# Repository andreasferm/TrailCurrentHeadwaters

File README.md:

# TrailCurrent In-Vehicle Compute

> [!CAUTION]
> **Personal fork adapting to a new module [Australis](https://github.com/andreasferm/TrailCurrentAustralis) with the aim to monitor 1-8 enclosed rooms in a dogtrailer** This is definitely a work in progress
> **The Radxa Dragon Q6A variant is a work in progress and is not recommended for use yet.** Further hardware and field testing is required before it should be considered shippable. Use the **CM5 build** for any real deployment.

Dockerized edge gateway with MQTT broker, tile server, and local dashboards. Part of the [TrailCurrent](https://trailcurrent.com) open-source vehicle platform.

## Quick Navigation

| I want to... | Go here |
|--------------|---------|
| Set up a development environment | [Development Setup](#development-setup) below |
| Build a CM5 image or deployment package | [Building for CM5 Devices](#building-for-cm5-devices) below |
| Flash and set up a new CM5 device | [CM5/SETUP.md](CM5/SETUP.md) |
| Update an existing device | [PI_DEPLOYMENT.md](PI_DEPLOYMENT.md) |
| Understand cloud OTA updates | [OTA_DEPLOYMENT_IMPLEMENTATION.md](OTA_DEPLOYMENT_IMPLEMENTATION.md#cloud-to-pi-ota-deployment-deployment-watcher) |

## Prerequisites

- **Hardware:** Raspberry Pi Compute Module 5 (CM5) on a standard carrier board with Waveshare RS485 CAN HAT (B) — no custom components or soldering required. The CM5 + carrier board replaces the previous Pi 5 + NVME Base + custom CAN HAT stack: it's more compact, more readily available, cheaper, and can be fully assembled from off-the-shelf parts.
- **Docker Engine** (or Docker Desktop) with the `compose` plugin and `buildx`
- **Git**

---

## Development Setup

This gets your local development environment running with hot-reload and debugging enabled. All services build from local Dockerfiles for the host platform.

### Step 1: Clone and configure environment

```bash
git clone <REPO_URL>
cd TrailCurrentHeadwaters
git config core.hooksPath .githooks
docker buildx use default
cp .env.example .env
```

### Step 2: Generate secure random values

```bash
# Generate ENCRYPTION_KEY (64 character hex string)
openssl rand -hex 32
```

Copy the value into `ENCRYPTION_KEY` in `.env`.

### Step 3: Edit `.env` and set your values

- `ENCRYPTION_KEY` - Paste the value from step 2
- `ADMIN_PASSWORD` - Strong password for system admin access
- `MQTT_USERNAME` - Username for MQTT broker
- `MQTT_PASSWORD` - Password for MQTT broker (plain text - auto-added to broker at startup)
- `TLS_CERT_HOSTNAME` - Your device's hostname (e.g., `trailcurrent01.local`)

### Step 4: Generate SSL certificates

```bash
./scripts/generate-certs.sh
# Select option 1 for Development or option 2 for Production
```

See [SSL Certificate Generation](#ssl-certificate-generation) for details.

### Step 5: Obtain map tiles

The tileserver requires a pre-generated mbtiles file to serve map data.

```bash
mkdir -p data/tileserver
# Place your tiles file at: data/tileserver/map.mbtiles
```

**How to get tiles:**
- **Download from OpenStreetMap:** Use the [PbfTileConverter](https://github.com/onthegomap/planetiler) utility or a service like [Protomaps](https://protomaps.com/) to generate tiles from OSM data (see [DOCS/UpdatingMapTiles.md](DOCS/UpdatingMapTiles.md))
- **Copy from a team member:** Copy `map.mbtiles` from an existing machine

A single US state (~200 MB - 2 GB) works fine for development. Full US coverage is ~10-25 GB.

### Step 6: Build and start in development mode

```bash
docker compose -f docker-compose.yml -f docker-compose.dev.yml up -d --build
```

The `--build` flag ensures all images are built from local Dockerfiles for your host platform. Development mode enables:
- Hot-reload for frontend and backend code changes
- Node.js debug port (9229) for VSCode debugger attachment
- MongoDB accessible on localhost:27017
- Tileserver styles hot-reload

Containers will automatically:
- Create the mosquitto password file from your credentials
- Initialize all services with consistent credentials
- Mount the SSL certificates for HTTPS/MQTTS communication
- Load map tiles from the mbtiles file

### Verification Checklist

After startup, verify all services are healthy:

```bash
# All 5 containers should be running
docker compose ps

# Frontend loads
curl -k https://localhost/

# Tileserver healthy
curl http://localhost:8080/health

# Map style served
curl -s http://localhost:8080/styles/3d-dark/style.json | head -5

# Font glyphs available
curl -s -o /dev/null -w "%{http_code}" "http://localhost:8080/fonts/Noto%20Sans%20Regular/0-255.pbf"
# Expected: 200
```

**Access the web UI:** https://localhost (accept the self-signed certificate warning)

### Security Notes

- `.env` is in `.gitignore` - will never be committed
- Use strong, randomly generated passwords for all credentials
- All values in `.env.example` are placeholders only
- Passwords are auto-hashed/auto-configured at container startup

---

## Building for CM5 Devices

There are two ways to get the application onto a CM5 device:

### Option A: Build a Complete CM5 Image (Recommended for New Devices)

The CM5 image includes everything — OS, Docker, application containers, map
tiles, and configuration. After flashing, the user just sets passwords via
an interactive wizard on first SSH login.

**Prerequisites (files not in the repo that you must provide):**

| File | How to get it |
|------|---------------|
| `images/*.tar` | Run `./build-and-save-images.sh` (builds ARM64 Docker images) |
| `data/tileserver/map.mbtiles` | Download from OSM data or copy from a team member (see [DOCS/UpdatingMapTiles.md](DOCS/UpdatingMapTiles.md)) |

**Build the image:**
```bash
# 1. Build ARM64 Docker images (~10 min first time)
./build-and-save-images.sh

# 2. Ensure map.mbtiles exists at data/tileserver/map.mbtiles

# 3. Build the CM5 image (bakes in Docker images, map tiles, app code, configs)
cd CM5/image
sudo ./build.sh myuser mypassword
```

The output image (~28 GB) is flashed to NVMe via `dd`. See [CM5/SETUP.md](CM5/SETUP.md)
for the full flashing and setup procedure.

### Option B: Build a Deployment Package (For Updating Existing Devices)

For updating devices that already have an image flashed, create an offline
deployment zip:

```bash
# Build everything and create the zip
./create-deployment-package.sh --version=1.0.0
```

This will:
1. Build all 4 service images for `linux/arm64` (plus pull `mongo:7`)
2. Save images as `.tar` files in `images/`
3. Fetch MCU firmware from GitHub releases (if available)
4. Package everything into `trailcurrent-deployment-1.0.0.zip`

**Transfer and deploy to device:**
```bash
scp trailcurrent-deployment-1.0.0.zip myuser@headwaters.local:~
# On the device:
unzip -o trailcurrent-deployment-1.0.0.zip && ./deploy.sh
```

Replace `myuser` with the username configured when the CM5 image was built.

See [PI_DEPLOYMENT.md](PI_DEPLOYMENT.md) for detailed deployment instructions.

> **Note:** `build-and-save-images.sh` is a prerequisite for both options.
> The CM5 image build (`build.sh`) and the deployment package
> (`create-deployment-package.sh`) both consume the `images/*.tar` files
> it produces.

---

## Architecture

### Services

The application runs 5 Docker containers:

| Service | Purpose |
|---------|---------|
| **frontend** | nginx serving the MapLibre GL PWA (HTTPS on port 443) |
| **backend** | Node.js Express API with MQTT, CAN bridge, and cloud bridge |
| **mosquitto** | Eclipse Mosquitto MQTT broker (TLS on port 8883) |
| **mongodb** | MongoDB 7 document database |
| **tileserver** | Custom vector tile server with styles, fonts, and sprites |

### CAN Bus Bridge

The backend includes a built-in CAN bridge service (`src/services/can-bridge.js`) that:
- Subscribes to `can/inbound` MQTT messages from the host-side Python CAN-to-MQTT bridge
- Routes by CAN identifier and parses bit-array data into structured JSON
- Publishes to `local/*` MQTT topics (lights, relays, energy, GPS, air quality, leveling)
- Sends outbound CAN commands for light toggles, brightness, and relay control

### Cloud Bridge

When cloud synchronization is enabled in Settings, the backend connects a second MQTT client to the Farwatch cloud broker over cellular LTE (`src/services/cloud-bridge.js`):

- **Cloud to Local (Commands):** `rv/lights/N/command` triggers CAN toggle, `rv/thermostat/command` passes through to local
- **Cloud to Local (Proximity):** `rv/proximity/event` and `rv/proximity/status` are forwarded to `local/proximity/*` and broadcast via WebSocket. These events are published by the Farwatch proximity engine when a registered phone enters or leaves a distance zone around the vehicle. The automation rules themselves execute on Farwatch (publishing light/relay commands via the existing `rv/lights/*/command` and `rv/relays/*/command` topics), so no rule processing happens on the vehicle. The forwarded events are available for future Overlook UI display.
- **Local to Cloud (Status):** Forwarded using three data-saving mechanisms to stay within a 10 GB/month cellular budget:
  - **Change detection** — Messages identical to the last-sent value are suppressed. Lights and relays (65% of raw CAN traffic) broadcast unchanged state every second; change detection eliminates ~99% of these.
  - **Tiered intervals** — Each data type has a minimum send interval: immediate (lights, relays, thermostat — on change only), 5 seconds (energy, GPS position — with threshold bypass for significant changes), 15 seconds (altitude, air quality, leveling), 30 seconds (system stats). GPS time is not forwarded (Farwatch has its own clock).
  - **Heartbeat** — Every 20 seconds, all last-known state is republished to the cloud as a safety net for connection-level failures. In normal operation, state changes are forwarded immediately via MQTT QoS 1.
- **Config sync:** System config snapshot published as retained message on cloud connect, plus forced full-state heartbeat on reconnect

### SMS Notifications

The system can send SMS text messages through a cellular router's `sendsms` command via SSH. This is configured in **Settings > SMS Notifications**:

- **Phone Number** — Destination phone number (e.g., `+15551234567`)
- **Router IP Address** — LAN IP of the cellular router
- **SSH Private Key** — Private key for passwordless SSH as `root` to the router

To set up SSH access to the router:

```bash
# Generate an SSH key (if you don't already have one)
ssh-keygen -t ed25519

# Copy the public key to the router
ssh-copy-id root@<router-ip>
```

The private key (typically `~/.ssh/id_ed25519`) is pasted into the settings field and stored encrypted in the database. Use the **Send Test SMS** button to verify the configuration.

### Alarm System

The alarm feature provides SMS notifications when device state changes are detected. A toggle on the home screen enables/disables the alarm. When enabled, the system monitors CAN bus status messages and sends an SMS when a device's state changes.

**How it works:**

1. The MQTT service tracks the last known state of each device from CAN bus messages
2. When a new status message reports a different state than the cached value, the alarm fires
3. Notifications are grouped by device type, each with its own independent cooldown (default 60 seconds)
4. Multiple state changes within the same group's cooldown window result in a single SMS

**Alarm groups:**

| Group | Source | Trigger |
|-------|--------|---------|
| `light` | PDM/Torrent light controllers | Light state change (on/off) |
| `relay` | Switchback relay modules | Relay state change (on/off) |
| `energy` | Energy monitor | (future) |
| `airquality` | Air quality sensor | (future) |
| `thermostat` | Thermostat | (future) |
| `level` | Leveling system | (future) |
| `gps` | GPS/GNSS | (future) |

Groups are defined in `MqttService.ALARM_GROUPS` in `containers/backend/src/mqtt.js`. Each group can be configured with its own cooldown period, and the architecture supports per-group settings for whether every event or only the first event in a window should trigger an SMS.

**SMS message content:**

- If cloud is enabled: `Unexpected event occurred, check Farwatch for details <cloud_url>`
- If cloud is not enabled: `Unexpected event occurred`

**Requirements:** SMS must be configured and enabled in Settings for alarm notifications to be sent.

### Host-Side Services

Python scripts running as systemd services on the host (outside Docker):
- `can-to-mqtt.py` — Bridges the physical CAN bus (`can0`) to MQTT topics (`can/inbound`, `can/outbound`)
- `discovery-mdns.py` — Discovers MCU modules on the local network via mDNS
- `deployment-watcher.py` — Monitors for OTA deployment updates from the cloud

---

## Project Structure

```
containers/          Dockerfiles for each service
  frontend/          nginx + MapLibre GL web UI
  backend/           Node.js Express API + CAN bridge + cloud bridge
  mosquitto/         Eclipse Mosquitto MQTT broker
  tileserver/        Custom tile server (styles, fonts, sprites)
config/              Version-controlled service configurations
  mosquitto/         mosquitto.conf
data/                Runtime data (gitignored)
  keys/              TLS certificates
  tileserver/        map.mbtiles (~25 GB, not in repo)
images/              ARM64 Docker image tarballs (gitignored, built by build-and-save-images.sh)
local_code/          Python host services (CAN-to-MQTT bridge, deployment watcher, OTA helpers)
scripts/             Utility scripts (cert generation)
CM5/                 CM5 image build system, flashing tools, setup guide
```

**Docker Compose files:**
- `docker-compose.yml` — Production orchestration (5 services)
- `docker-compose.dev.yml` — Development overrides (hot-reload, debug ports)

---

## SSL Certificate Generation

The application uses TLS/SSL for secure communication. Certificates must be generated before running `docker compose up`. The `scripts/generate-certs.sh` script supports two modes:

### Quick Reference

```bash
# Interactive mode (prompts for selection)
./scripts/generate-certs.sh

# Non-interactive mode (development)
./scripts/generate-certs.sh 1

# Non-interactive mode (production)
./scripts/generate-certs.sh 2

# Using environment variable
CERT_MODE=2 ./scripts/generate-certs.sh

# Show help
./scripts/generate-certs.sh --help
```

### Development Certificates (Local Testing)

For local development with `localhost` or `127.0.0.1`:

```bash
./scripts/generate-certs.sh 1
```

**Development certificates include:**
- DNS names: `localhost`, plus your `TLS_CERT_HOSTNAME` from `.env`
- IP addresses: `127.0.0.1`, `::1` (IPv6 localhost)

**Access locally:**
```
https://localhost           - Frontend (HTTPS)
```

Accept the self-signed certificate warning in your browser (one-time).

### Production Certificates (Deployment)

For deployed devices accessed from other machines on the network:

1. **Set your device's hostname** in `.env`:
   ```
   TLS_CERT_HOSTNAME=trailcurrent01.local
   ```

2. **Generate production certificates:**
   ```bash
   ./scripts/generate-certs.sh 2
   ```

3. **Install the CA certificate** (`data/keys/ca.crt`) on devices that will access the web UI.

4. **Access from the network:**
   ```
   https://trailcurrent01.local       - Web UI
   mqtts://trailcurrent01.local:8883  - MQTT broker
   ```

### Regenerating Certificates

Run the script anytime to regenerate. It will prompt before overwriting existing certificates and create backups.

```bash
./scripts/generate-certs.sh
docker compose restart
```

Certificates are automatically protected by `.gitignore`. Never commit them to version control.

---

## Docker

### Running Containers

```bash
# Development mode (hot-reload, debug ports) — always use --build to ensure local images
docker compose -f docker-compose.yml -f docker-compose.dev.yml up -d --build

# Production mode (after verification)
docker compose up -d --build
```

### Docker Networking

**MongoDB Access:**
- Services communicate via Docker's internal network: `mongodb:27017`
- MongoDB is NOT exposed to localhost (127.0.0.1)
- To access MongoDB from your host: `docker compose exec mongodb mongosh`

Docker containers use service names for inter-container communication.

### Data Persistence

The `data/` directory contains all persistent application data:

- **SSL certificates** (`data/keys/`) — Generated once, valid for 10 years
- **Map tiles** (`data/tileserver/map.mbtiles`) — Set up once, rarely updated
- **MongoDB** — Named volume `mongodb-data`, persists across rebuilds

**Never delete `data/` during updates** unless performing a complete reset. All data persists across container rebuilds.

**Updating the Application (No Data Loss):**
```bash
git pull
docker compose -f docker-compose.yml -f docker-compose.dev.yml up -d --build
# Certificates, .env, and map tiles are preserved
```

---

## Debugging

### VSCode Node.js Debugger

The backend Node.js server can be debugged using VSCode's built-in debugger. The setup uses `--inspect-brk` to pause the application at startup, waiting for the debugger to attach before continuing execution.

#### Quick Start

1. **Open the project in VSCode** (if not already open)

2. **Start debugging:**
   - Open the Debug panel (Ctrl+Shift+D / Cmd+Shift+D)
   - Select "Backend Debug" from the dropdown
   - Click the green "Start Debugging" button (or press F5)

3. **What happens automatically:**
   - Docker containers start in development mode (`docker-compose -f docker-compose.yml -f docker-compose.dev.yml up`)
   - Backend container starts with `--inspect-brk=0.0.0.0:9229` (pauses at startup)
   - VSCode automatically attaches the debugger to port 9229
   - Application resumes and you can now set breakpoints

4. **Stop debugging:**
   - Press Shift+F5 or click the stop button in the debug panel
   - Docker containers are automatically stopped (`docker-compose down`)

#### Manual Debugging (Without VSCode Integration)

```bash
# Start containers in development mode
docker compose -f docker-compose.yml -f docker-compose.dev.yml up

# In VSCode, attach manually:
# - Open Debug panel (Ctrl+Shift+D)
# - Select "Backend Debug"
# - Click "Start Debugging" (F5)
```

#### Debugging Configuration

The debugging setup is configured in `.vscode/launch.json`:

```json
{
  "name": "Backend Debug",
  "type": "node",
  "request": "attach",
  "port": 9229,
  "address": "localhost",
  "restart": true,
  "skipFiles": ["<node_internals>/**"],
  "outFiles": ["${workspaceFolder}/containers/backend/src/**/*.js"]
}
```

#### Troubleshooting

**"Connection refused" error:**
- Ensure containers are running: `docker compose ps`
- Check backend container logs: `docker compose logs backend`
- Verify port 9229 is exposed: `docker compose port backend 9229`

**Breakpoints not being hit:**
- Verify the file path matches exactly (case-sensitive on Linux)
- Check development mode: `docker compose config | grep "NODE_ENV"`

**Backend container exits immediately:**
- Check logs: `docker compose logs backend`
- Ensure `.env` file is set up correctly
- Verify MongoDB: `docker compose logs mongodb`

**Mosquitto or other containers failing to start:**
- Check logs: `docker compose logs mosquitto`
- Certificate permissions: `chmod 644 data/keys/*.key data/keys/*.crt data/keys/*.pem`

**Port conflicts:**
- Clean up: `docker system prune -f --volumes`
- Verify no containers running: `docker ps -a`
- Restart Docker: `sudo systemctl restart docker`

#### Tips for Effective Debugging

1. **Breakpoint in startServer()** in `src/index.js` to debug initialization
2. **Route breakpoints** in route handlers (e.g., `src/routes/thermostat.js`)
3. **MQTT debugging** via breakpoints in `src/mqtt.js`
4. **CAN bridge debugging** via breakpoints in `src/services/can-bridge.js`
5. **Conditional breakpoints**: Right-click a breakpoint to set conditions
6. **Logpoints**: Right-click line number to log values without pausing

---

## Third-Party Components

TrailCurrent Headwaters is MIT-licensed, but the image-build tooling for the Radxa Dragon Q6A target vendors the **Radxa SDK** ([`RadxaOS-SDK/rsdk`](https://github.com/RadxaOS-SDK/rsdk)) under its original **GPL-3.0-or-later** license. The vendored tree lives at [`RADXAQ6A/image/rsdk/`](RADXAQ6A/image/rsdk/) with its upstream [`LICENSE`](RADXAQ6A/image/rsdk/LICENSE) preserved. rsdk is a build-time tool — it produces the flashable image but is not linked into or shipped inside any TrailCurrent runtime component, so the MIT licensing of the TrailCurrent sources is unaffected.

---

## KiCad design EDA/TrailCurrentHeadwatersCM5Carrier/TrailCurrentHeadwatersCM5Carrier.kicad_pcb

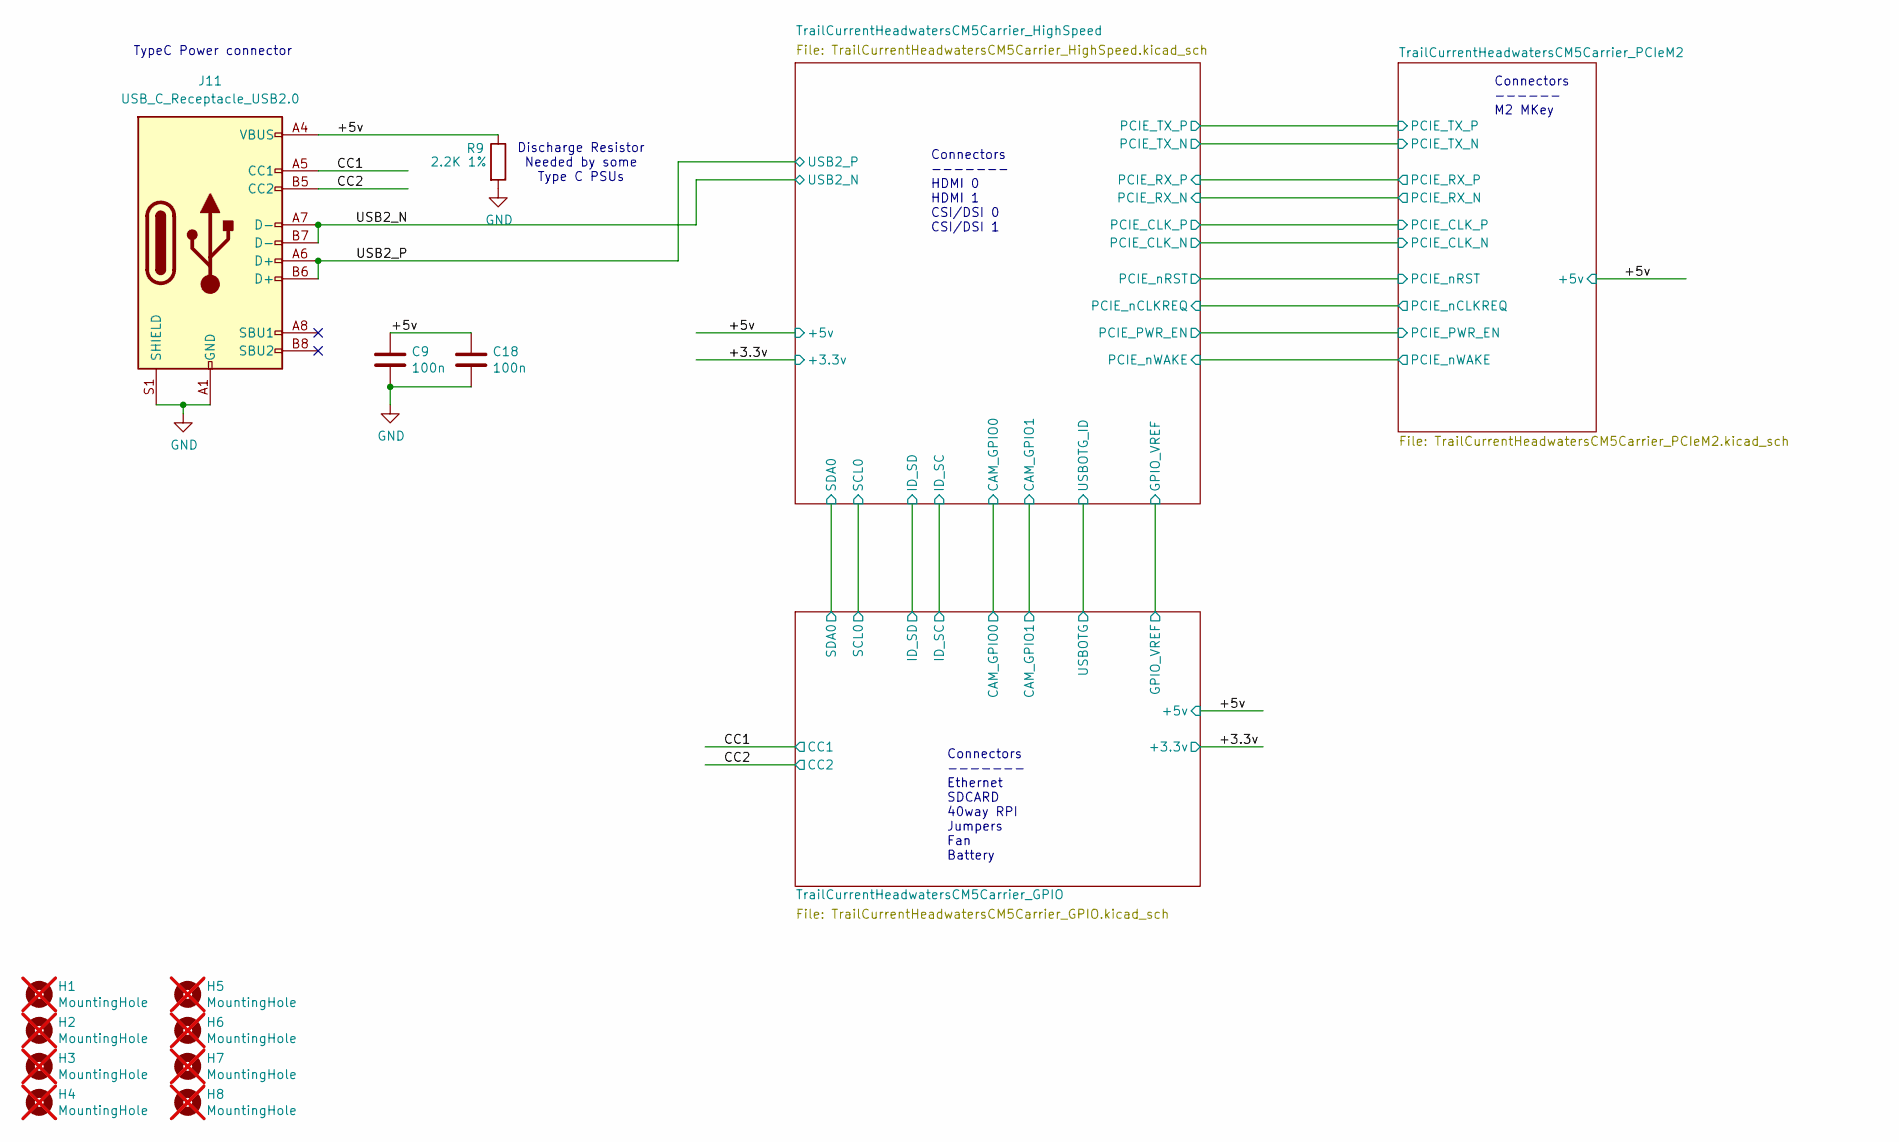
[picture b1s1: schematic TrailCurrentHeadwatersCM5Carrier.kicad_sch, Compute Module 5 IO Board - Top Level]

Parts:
C9, C18: 100n; C_0402_1005Metric; Part Description 0.1uF 10% 16V Ceramic Capacitor X7R 040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
H1, H2, H3, H4, H5, H6, H7, H8: MountingHole; MountingHole_2.7mm_M2.5_DIN965; Part Description M2.5 mounting hole; not fitted
J11: USB_C_Receptacle_USB2.0; USB_C_Receptacle_GCT_USB4105-xx-A_16P_TopMnt_Horizontal; Part Description USBC USB2 data and power connector
R9: 2.2K 1%; R_0402_1005Metric; Part Description Resistor 2.2K M1005 1% 63mW

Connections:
/+5v: C9.1, C18.1, J11.A4 (VBUS), J11.A9 (VBUS), J11.B4 (VBUS), J11.B9 (VBUS), R9.1; also elsewhere on the board
/CC1: J11.A5 (CC1); also elsewhere on the board
/CC2: J11.B5 (CC2); also elsewhere on the board
/USB2_N: J11.A7 (D-), J11.B7 (D-); also elsewhere on the board
/USB2_P: J11.A6 (D+), J11.B6 (D+); also elsewhere on the board
GND: C9.2, C18.2, J11.A1 (GND), J11.A12 (GND), J11.B1 (GND), J11.B12 (GND), J11.S1 (SHIELD), R9.2; also elsewhere on the board

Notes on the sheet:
Connectors ------- Ethernet SDCARD 40way RPI Jumpers Fan Battery
Connectors ------ M2 MKey
Discharge Resistor Needed by some Type C PSUs
TypeC Power connector
Connectors ------- HDMI 0 HDMI 1 CSI/DSI 0 CSI/DSI 1

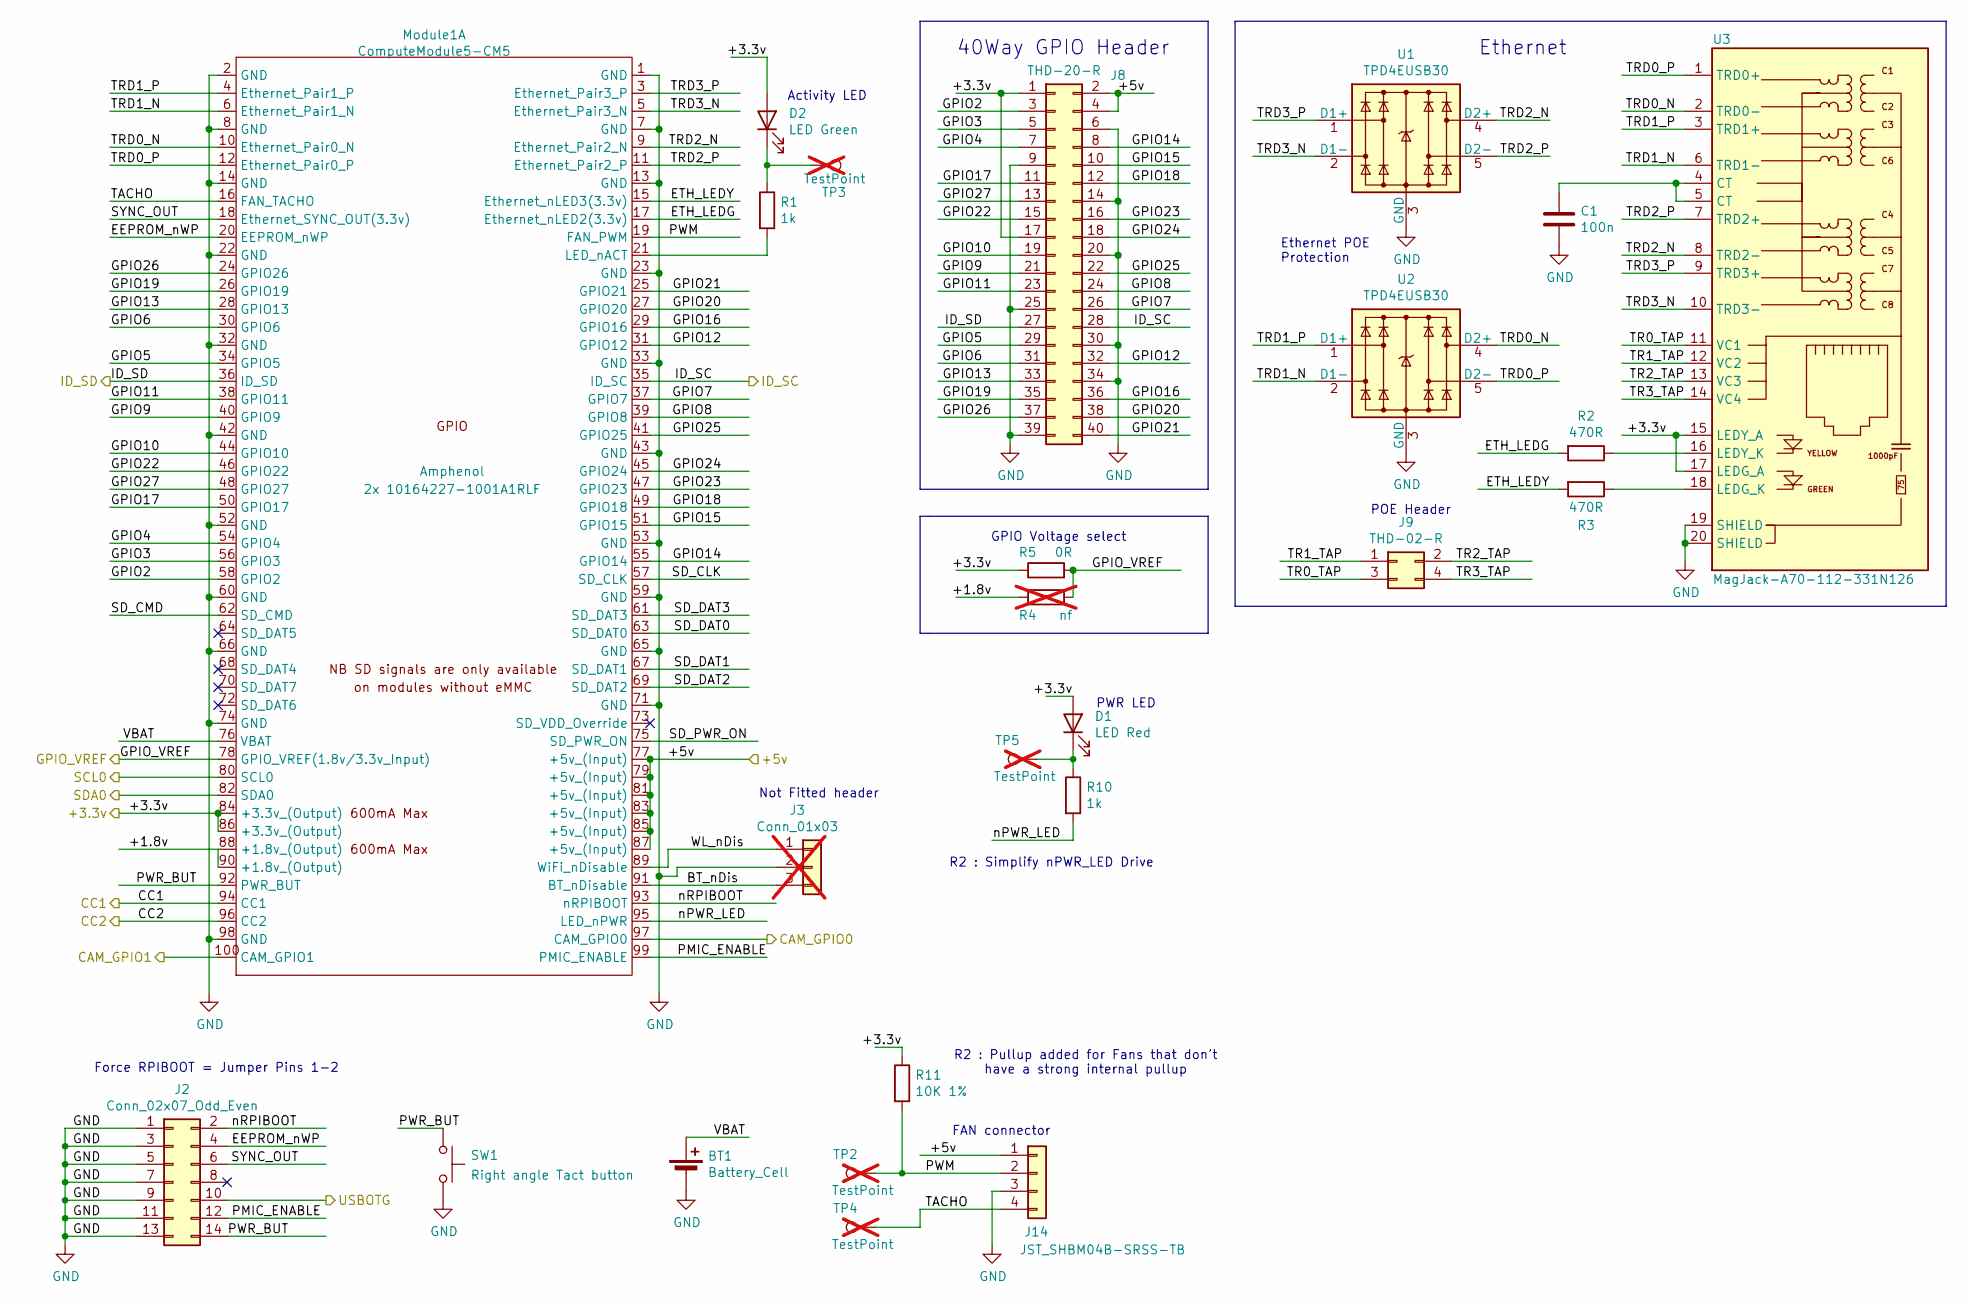
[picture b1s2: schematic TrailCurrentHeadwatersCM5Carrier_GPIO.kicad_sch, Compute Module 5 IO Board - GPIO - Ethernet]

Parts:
BT1: Battery_Cell; BatteryHolder_Keystone_3034_1x20mm; Part Description Battery Retainer Coin, 20.0mm 1 Cell SM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
C1: 100n; C_0402_1005Metric; Part Description 0.1uF 10% 16V Ceramic Capacitor X7R 040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
D1: LED Red; LED_0603_1608Metric; Part Description Red 620nm LED Indication - Discrete 2.2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
D2: LED Green; LED_0603_1608Metric; Part Description Green 572nm LED Indication - Discrete 2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
J2: Conn_02x07_Odd_Even; PinHeader_2x07_P2.54mm_Vertical; Part Description PinHeader_2x07_P2.54mm_Vertical
J3: Conn_01x03; PinHeader_1x03_P2.54mm_Vertical; Part Description 3pin 0.1" connector; not fitted
J8: THD-20-R; PinHeader_2x20_P2.54mm_Vertical; Part Description PinHeader_2x20_P2.54mm_Vertical
J9: THD-02-R; PinHeader_2x02_P2.54mm_Vertical; Part Description PinHeader_2x02_P2.54mm_Vertical
J14: JST_SHBM04B-SRSS-TB; JST_SH_BM04B-SRSS-TB_1x04-1MP_P1.00mm_Vertical; Part Description 4 pin vertical 1mm pitch connector
Module1: ComputeModule5-CM5; Raspberry-Pi-5-Compute-Module; Part Description 100 Position Connector Receptacle, Cent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
R1, R10: 1k; R_0402_1005Metric; Part Description Resistor 1K M1005 1% 63mW
R2, R3: 470R; R_0402_1005Metric; Part Description Resistor 470R M1005 1% 63mW
R4: nf; R_0805_2012Metric_Pad1.20x1.40mm_HandSolder; not fitted
R5: 0R; R_0805_2012Metric_Pad1.20x1.40mm_HandSolder; Part Description Resistor 0R M2012 5%
R11: 10K 1%; R_0402_1005Metric; Part Description Resistor 10K M1005 1% 63mW
SW1: Right angle Tact button; SW_Tactile_SPST_Angled_PTS645Vx58-2LFS; Part Description Right angle through hole Tact switch
TP2, TP3, TP4, TP5: TestPoint; TestPoint_Pad_2.0x2.0mm; Part Description Test point; not fitted
U1, U2: TPD4EUSB30; USON-10_2.5x1.0mm_P0.5mm; Part Description Quad TVS diode for high speed signals (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
U3: MagJack-A70-112-331N126; TRJG0926HENL; Part Description Gigabit Ethernet Magjack

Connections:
/+3.3v: D1.2 (A), D2.2 (A), J8.1, J8.17, Module1.84 (+3.3v_(Output)), Module1.86 (+3.3v_(Output)), R5.1, R11.1, U3.15 (LEDY_A), U3.17 (LEDG_A); also elsewhere on the board
/+5v: J8.2, J8.4, J14.1, Module1.77 (+5v_(Input)), Module1.79 (+5v_(Input)), Module1.81 (+5v_(Input)), Module1.83 (+5v_(Input)), Module1.85 (+5v_(Input)), Module1.87 (+5v_(Input)); also elsewhere on the board
/CC1: Module1.94 (CC1); also elsewhere on the board
/CC2: Module1.96 (CC2); also elsewhere on the board
/TrailCurrentHeadwatersCM5Carrier_GPIO/+1.8v: Module1.88 (+1.8v_(Output)), Module1.90 (+1.8v_(Output)), R4.1
/TrailCurrentHeadwatersCM5Carrier_GPIO/BT_nDis: J3.3, Module1.91 (BT_nDisable)
/TrailCurrentHeadwatersCM5Carrier_GPIO/CAM_GPIO0: Module1.97 (CAM_GPIO0); also elsewhere on the board
/TrailCurrentHeadwatersCM5Carrier_GPIO/CAM_GPIO1: Module1.100 (CAM_GPIO1); also elsewhere on the board
/TrailCurrentHeadwatersCM5Carrier_GPIO/EEPROM_nWP: J2.4, Module1.20 (EEPROM_nWP)
/TrailCurrentHeadwatersCM5Carrier_GPIO/ETH_LEDG: Module1.17 (Ethernet_nLED2(3.3v)), R2.2
/TrailCurrentHeadwatersCM5Carrier_GPIO/ETH_LEDY: Module1.15 (Ethernet_nLED3(3.3v)), R3.2
/TrailCurrentHeadwatersCM5Carrier_GPIO/GPIO2: J8.3, Module1.58 (GPIO2)
/TrailCurrentHeadwatersCM5Carrier_GPIO/GPIO3: J8.5, Module1.56 (GPIO3)
/TrailCurrentHeadwatersCM5Carrier_GPIO/GPIO4: J8.7, Module1.54 (GPIO4)
/TrailCurrentHeadwatersCM5Carrier_GPIO/GPIO5: J8.29, Module1.34 (GPIO5)
/TrailCurrentHeadwatersCM5Carrier_GPIO/GPIO6: J8.31, Module1.30 (GPIO6)
/TrailCurrentHeadwatersCM5Carrier_GPIO/GPIO7: J8.26, Module1.37 (GPIO7)
/TrailCurrentHeadwatersCM5Carrier_GPIO/GPIO8: J8.24, Module1.39 (GPIO8)
/TrailCurrentHeadwatersCM5Carrier_GPIO/GPIO9: J8.21, Module1.40 (GPIO9)
/TrailCurrentHeadwatersCM5Carrier_GPIO/GPIO10: J8.19, Module1.44 (GPIO10)
/TrailCurrentHeadwatersCM5Carrier_GPIO/GPIO11: J8.23, Module1.38 (GPIO11)
/TrailCurrentHeadwatersCM5Carrier_GPIO/GPIO12: J8.32, Module1.31 (GPIO12)
/TrailCurrentHeadwatersCM5Carrier_GPIO/GPIO13: J8.33, Module1.28 (GPIO13)
/TrailCurrentHeadwatersCM5Carrier_GPIO/GPIO14: J8.8, Module1.55 (GPIO14)
/TrailCurrentHeadwatersCM5Carrier_GPIO/GPIO15: J8.10, Module1.51 (GPIO15)
/TrailCurrentHeadwatersCM5Carrier_GPIO/GPIO16: J8.36, Module1.29 (GPIO16)
/TrailCurrentHeadwatersCM5Carrier_GPIO/GPIO17: J8.11, Module1.50 (GPIO17)
/TrailCurrentHeadwatersCM5Carrier_GPIO/GPIO18: J8.12, Module1.49 (GPIO18)
/TrailCurrentHeadwatersCM5Carrier_GPIO/GPIO19: J8.35, Module1.26 (GPIO19)
/TrailCurrentHeadwatersCM5Carrier_GPIO/GPIO20: J8.38, Module1.27 (GPIO20)
/TrailCurrentHeadwatersCM5Carrier_GPIO/GPIO21: J8.40, Module1.25 (GPIO21)
/TrailCurrentHeadwatersCM5Carrier_GPIO/GPIO22: J8.15, Module1.46 (GPIO22)
/TrailCurrentHeadwatersCM5Carrier_GPIO/GPIO23: J8.16, Module1.47 (GPIO23)
/TrailCurrentHeadwatersCM5Carrier_GPIO/GPIO24: J8.18, Module1.45 (GPIO24)
/TrailCurrentHeadwatersCM5Carrier_GPIO/GPIO25: J8.22, Module1.41 (GPIO25)
/TrailCurrentHeadwatersCM5Carrier_GPIO/GPIO26: J8.37, Module1.24 (GPIO26)
/TrailCurrentHeadwatersCM5Carrier_GPIO/GPIO27: J8.13, Module1.48 (GPIO27)
/TrailCurrentHeadwatersCM5Carrier_GPIO/GPIO_VREF: Module1.78 (GPIO_VREF(1.8v/3.3v_Input)), R4.2, R5.2; also elsewhere on the board
/TrailCurrentHeadwatersCM5Carrier_GPIO/ID_SC: J8.28, Module1.35 (ID_SC); also elsewhere on the board
/TrailCurrentHeadwatersCM5Carrier_GPIO/ID_SD: J8.27, Module1.36 (ID_SD); also elsewhere on the board
/TrailCurrentHeadwatersCM5Carrier_GPIO/PMIC_ENABLE: J2.12, Module1.99 (PMIC_ENABLE)
/TrailCurrentHeadwatersCM5Carrier_GPIO/PWM: J14.2, Module1.19 (FAN_PWM), R11.2, TP2.1
/TrailCurrentHeadwatersCM5Carrier_GPIO/PWR_BUT: J2.14, Module1.92 (PWR_BUT), SW1.1
/TrailCurrentHeadwatersCM5Carrier_GPIO/SD_CLK: Module1.57 (SD_CLK)
/TrailCurrentHeadwatersCM5Carrier_GPIO/SD_CMD: Module1.62 (SD_CMD)
/TrailCurrentHeadwatersCM5Carrier_GPIO/SD_DAT0: Module1.63 (SD_DAT0)
/TrailCurrentHeadwatersCM5Carrier_GPIO/SD_DAT1: Module1.67 (SD_DAT1)
/TrailCurrentHeadwatersCM5Carrier_GPIO/SD_DAT2: Module1.69 (SD_DAT2)
/TrailCurrentHeadwatersCM5Carrier_GPIO/SD_DAT3: Module1.61 (SD_DAT3)
/TrailCurrentHeadwatersCM5Carrier_GPIO/SD_PWR_ON: Module1.75 (SD_PWR_ON)
/TrailCurrentHeadwatersCM5Carrier_GPIO/SYNC_OUT: J2.6, Module1.18 (Ethernet_SYNC_OUT(3.3v))
/TrailCurrentHeadwatersCM5Carrier_GPIO/TACHO: J14.4, Module1.16 (FAN_TACHO), TP4.1
/TrailCurrentHeadwatersCM5Carrier_GPIO/TR0_TAP: J9.3, U3.11 (VC1)
/TrailCurrentHeadwatersCM5Carrier_GPIO/TR1_TAP: J9.1, U3.12 (VC2)
/TrailCurrentHeadwatersCM5Carrier_GPIO/TR2_TAP: J9.2, U3.13 (VC3)
/TrailCurrentHeadwatersCM5Carrier_GPIO/TR3_TAP: J9.4, U3.14 (VC4)
/TrailCurrentHeadwatersCM5Carrier_GPIO/TRD0_N: Module1.10 (Ethernet_Pair0_N), U2.4 (D2+), U2.7, U3.2 (TRD0-)
/TrailCurrentHeadwatersCM5Carrier_GPIO/TRD0_P: Module1.12 (Ethernet_Pair0_P), U2.5 (D2-), U2.6, U3.1 (TRD0+)
/TrailCurrentHeadwatersCM5Carrier_GPIO/TRD1_N: Module1.6 (Ethernet_Pair1_N), U2.2 (D1-), U2.9, U3.6 (TRD1-)
/TrailCurrentHeadwatersCM5Carrier_GPIO/TRD1_P: Module1.4 (Ethernet_Pair1_P), U2.1 (D1+), U2.10, U3.3 (TRD1+)
/TrailCurrentHeadwatersCM5Carrier_GPIO/TRD2_N: Module1.9 (Ethernet_Pair2_N), U1.4 (D2+), U1.7, U3.8 (TRD2-)
/TrailCurrentHeadwatersCM5Carrier_GPIO/TRD2_P: Module1.11 (Ethernet_Pair2_P), U1.5 (D2-), U1.6, U3.7 (TRD2+)
/TrailCurrentHeadwatersCM5Carrier_GPIO/TRD3_N: Module1.5 (Ethernet_Pair3_N), U1.2 (D1-), U1.9, U3.10 (TRD3-)
/TrailCurrentHeadwatersCM5Carrier_GPIO/TRD3_P: Module1.3 (Ethernet_Pair3_P), U1.1 (D1+), U1.10, U3.9 (TRD3+)
/TrailCurrentHeadwatersCM5Carrier_GPIO/USBOTG: J2.10; also elsewhere on the board
/TrailCurrentHeadwatersCM5Carrier_GPIO/VBAT: BT1.1 (+), Module1.76 (VBAT)
/TrailCurrentHeadwatersCM5Carrier_GPIO/WL_nDis: J3.1, Module1.89 (WiFi_nDisable)
/TrailCurrentHeadwatersCM5Carrier_GPIO/nPWR_LED: Module1.95 (LED_nPWR), R10.2
/TrailCurrentHeadwatersCM5Carrier_GPIO/nRPIBOOT: J2.2, Module1.93 (nRPIBOOT)
/TrailCurrentHeadwatersCM5Carrier_HighSpeed/SCL0: Module1.80 (SCL0); also elsewhere on the board
/TrailCurrentHeadwatersCM5Carrier_HighSpeed/SDA0: Module1.82 (SDA0); also elsewhere on the board
GND: BT1.2 (-), C1.2, J2.1, J2.3, J2.5, J2.7, J2.9, J2.11, J2.13, J3.2, J8.6, J8.9, J8.14, J8.20, J8.25, J8.30, J8.34, J8.39, J14.3, Module1.1 (GND), Module1.2 (GND), Module1.7 (GND), Module1.8 (GND), Module1.13 (GND), Module1.14 (GND), Module1.22 (GND), Module1.23 (GND), Module1.32 (GND), Module1.33 (GND), Module1.42 (GND), Module1.43 (GND), Module1.52 (GND), Module1.53 (GND), Module1.59 (GND), Module1.60 (GND), Module1.65 (GND), Module1.66 (GND), Module1.71 (GND), Module1.74 (GND), Module1.98 (GND), SW1.2, U1.3 (GND), U1.8 (GND), U2.3 (GND), U2.8 (GND), U3.19 (SHIELD), U3.20 (SHIELD); also elsewhere on the board
unnamed: C1.1, U3.4 (CT), U3.5 (CT)
unnamed: D1.1 (K), R10.1, TP5.1
unnamed: D2.1 (K), R1.1, TP3.1
unnamed: Module1.21 (LED_nACT), R1.2
unnamed: R3.1, U3.18 (LEDG_K)
unnamed: R2.1, U3.16 (LEDY_K)

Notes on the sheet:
40Way GPIO Header
Activity LED
R2 : Simplify nPWR_LED Drive
FAN connector
Ethernet POE Protection
GPIO Voltage select
R2 : Pullup added for Fans that don't have a strong internal pullup
Not Fitted header
POE Header
Force RPIBOOT = Jumper Pins 1-2
PWR LED
Ethernet

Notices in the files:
EDA/TrailCurrentHeadwatersCM5Carrier/TrailCurrentHeadwatersCM5Carrier.kicad_sch:
Copyright © 2024 Raspberry Pi Ltd.
